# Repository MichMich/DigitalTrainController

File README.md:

# DigitalTrainController

This repository contains all the sourcecode as well as the KiCad project for the [Digital Train Controller](http://michaelteeuw.nl/tagged/trainautomator) i built for my dad's model train. 

For more info about this project, check out my blog: http://michaelteeuw.nl/tagged/trainautomator

Feel free to use this code and PCB project, but keep in mind that it comes without ANY form of support. :)

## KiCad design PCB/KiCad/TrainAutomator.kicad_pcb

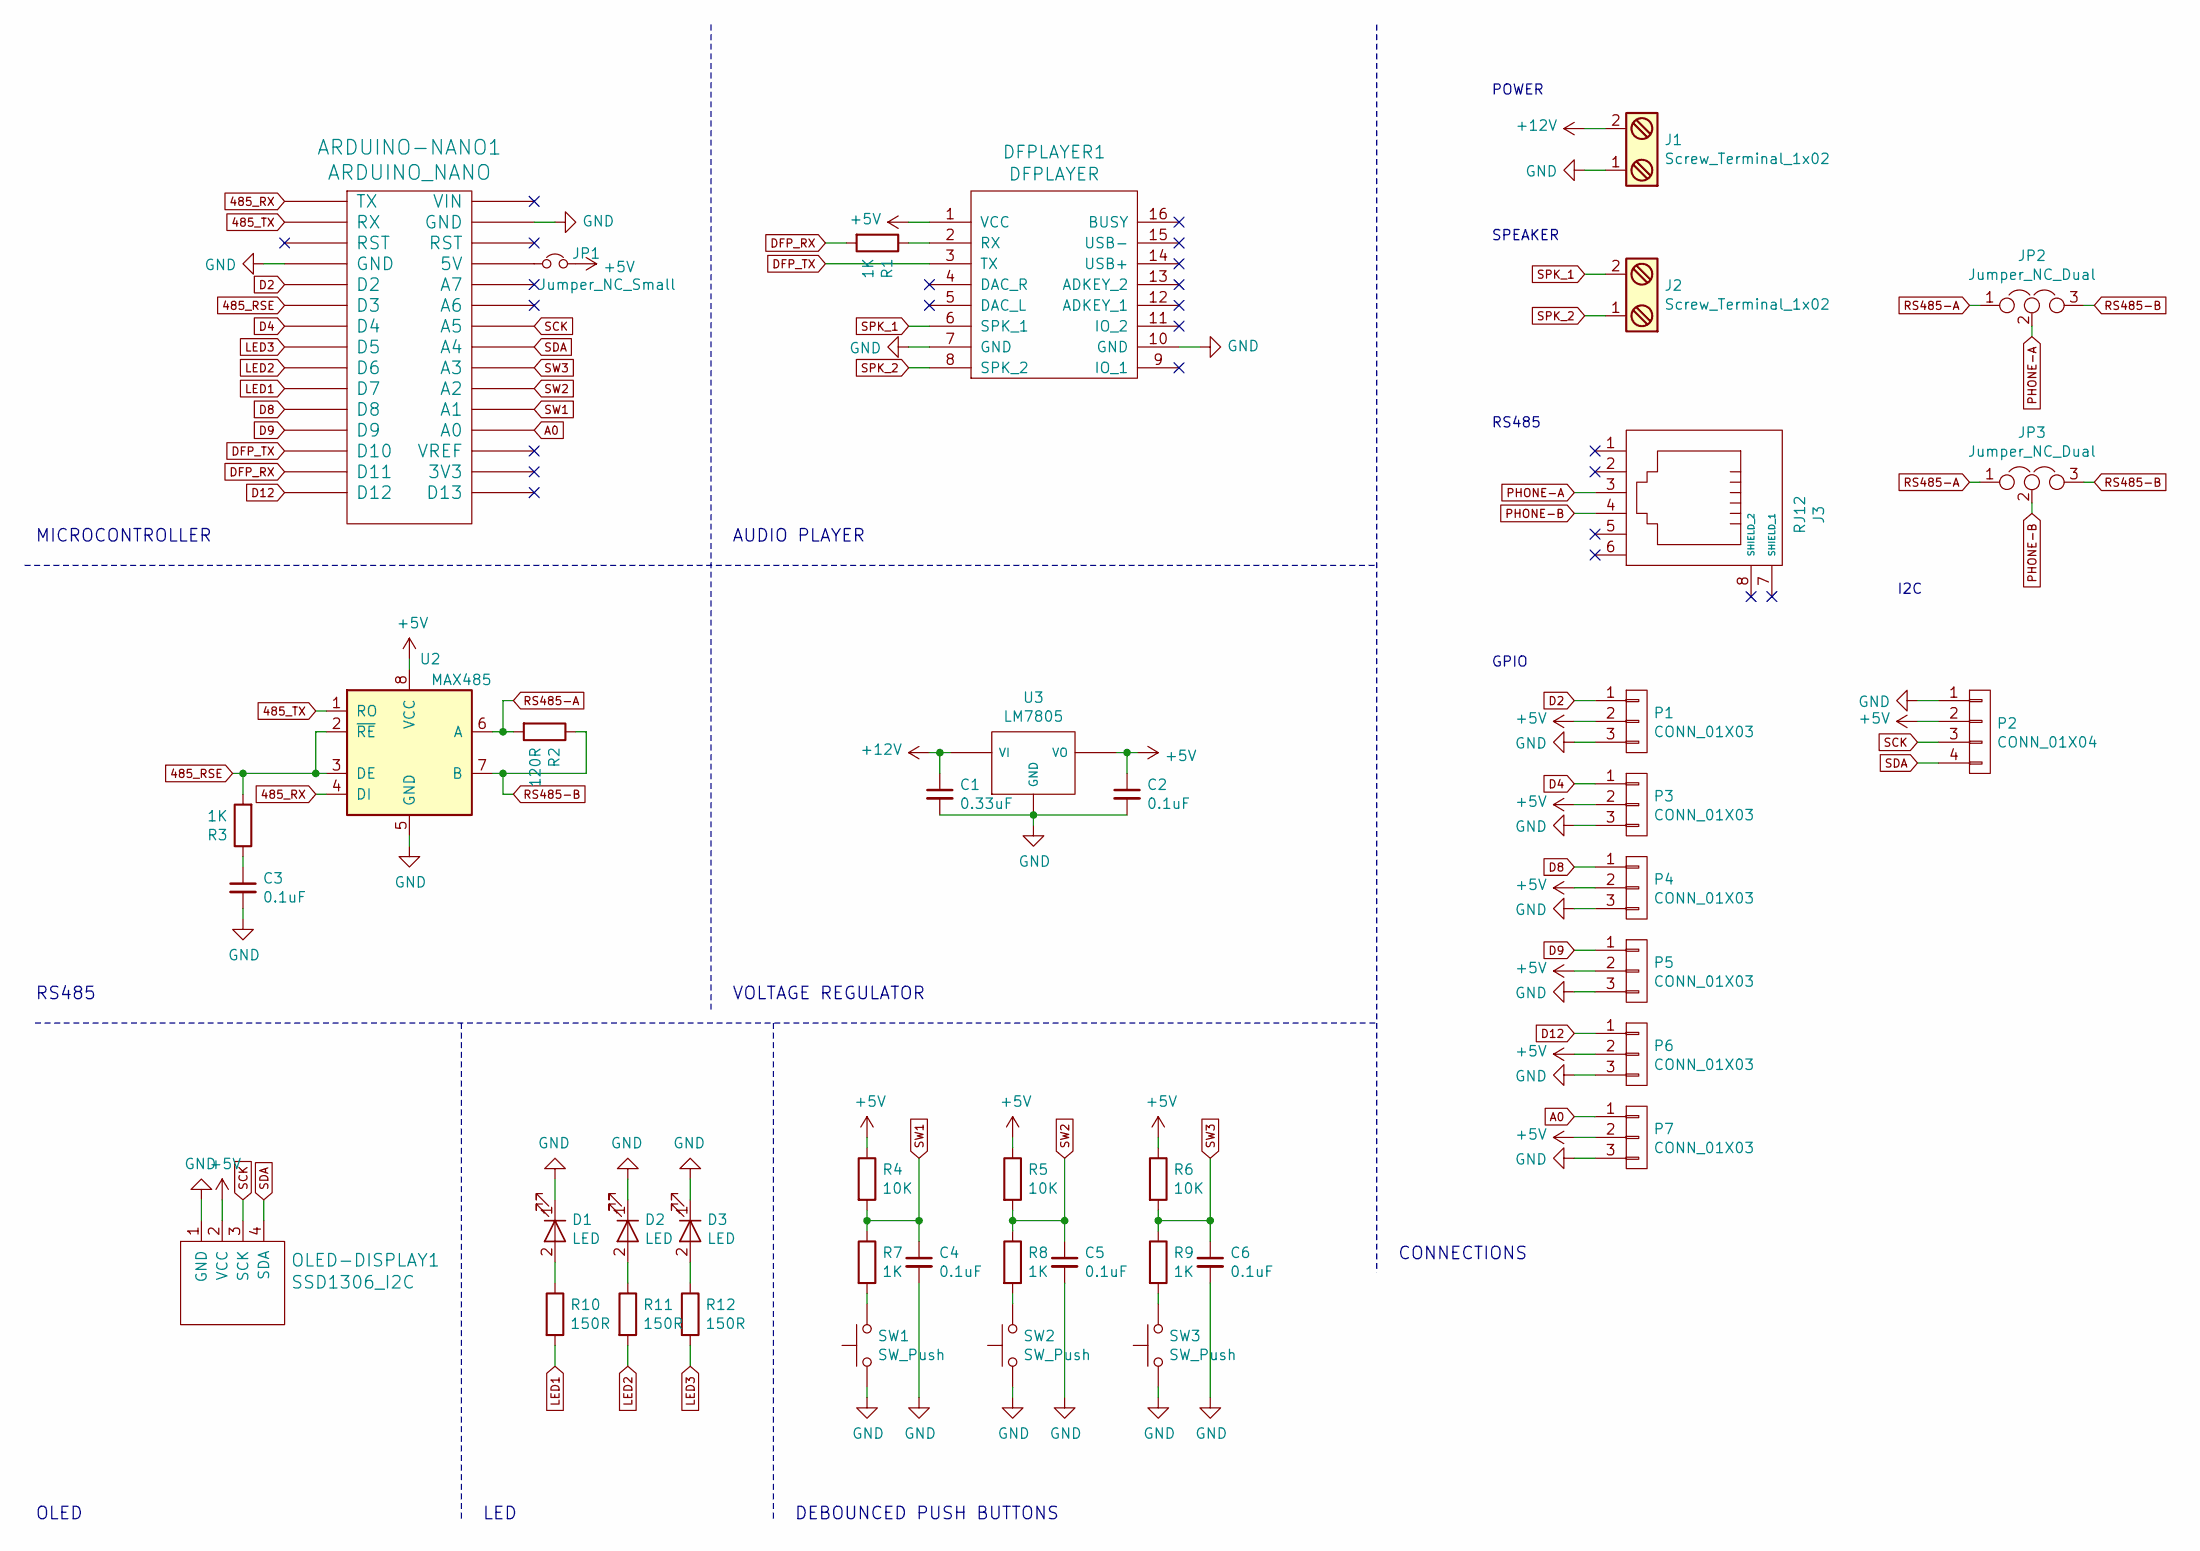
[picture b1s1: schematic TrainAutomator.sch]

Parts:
ARDUINO-NANO1: ARDUINO_NANO; ArduinoNano
C1: 0.33uF; C_0805_HandSoldering
C2, C3, C4, C5, C6: 0.1uF; C_0805_HandSoldering
D1, D2, D3: LED; LED_1206_HandSoldering
DFPLAYER1: DFPLAYER; DFPlayerMini
J1, J2: Screw_Terminal_1x02; TerminalBlock_4UCON_19963_02x3.5mm_Straight
J3: RJ12
JP1: Jumper_NC_Small; Pin_Header_Straight_1x02_Pitch2.00mm
JP2, JP3: Jumper_NC_Dual; DualJumper-NC
OLED-DISPLAY1: SSD1306_I2C; SSD1306-096-OLED-I2C
P1, P3, P4, P5, P6, P7: CONN_01X03; JST_PH_S3B-PH-K_03x2.00mm_Angled
P2: CONN_01X04; JST_PH_S4B-PH-K_04x2.00mm_Angled
R1, R3, R7, R8, R9: 1K; R_0805_HandSoldering
R2: 120R; R_0805_HandSoldering
R4, R5, R6: 10K; R_0805_HandSoldering
R10, R11, R12: 150R; R_0805_HandSoldering
SW1, SW2, SW3: SW_Push; SW_SPST_EVQPE1
U2: MAX485; SOIC-8_3.9x4.9mm_Pitch1.27mm
U3: LM7805; TO-263-2

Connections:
485_RSE: ARDUINO-NANO1.6 (D3), R3.2, U2.2 (~RE~), U2.3 (DE)
485_RX: ARDUINO-NANO1.1 (TX), U2.4 (DI)
485_TX: ARDUINO-NANO1.2 (RX), U2.1 (RO)
+5V: C2.1, DFPLAYER1.1 (VCC), JP1.2, OLED-DISPLAY1.2 (VCC), P1.2, P2.2, P3.2, P4.2, P5.2, P6.2, P7.2, R4.1, R5.1, R6.1, U2.8 (VCC), U3.3 (VO)
+12V: C1.1, J1.2, U3.1 (VI)
A0: ARDUINO-NANO1.19 (A0), P7.1
D2: ARDUINO-NANO1.5 (D2), P1.1
D4: ARDUINO-NANO1.7 (D4), P3.1
D8: ARDUINO-NANO1.11 (D8), P4.1
D9: ARDUINO-NANO1.12 (D9), P5.1
D12: ARDUINO-NANO1.15 (D12), P6.1
DFP_RX: ARDUINO-NANO1.14 (D11), R1.2
DFP_TX: ARDUINO-NANO1.13 (D10), DFPLAYER1.3 (TX)
GND: ARDUINO-NANO1.4 (GND), ARDUINO-NANO1.29 (GND), C1.2, C2.2, C3.2, C4.2, C5.2, C6.2, D1.1 (K), D2.1 (K), D3.1 (K), DFPLAYER1.7 (GND), DFPLAYER1.10 (GND), J1.1, OLED-DISPLAY1.1 (GND), P1.3, P2.1, P3.3, P4.3, P5.3, P6.3, P7.3, SW1.1, SW2.1, SW3.1, U2.5 (GND), U3.2 (GND)
LED1: ARDUINO-NANO1.10 (D7), R10.2
LED2: ARDUINO-NANO1.9 (D6), R11.2
LED3: ARDUINO-NANO1.8 (D5), R12.2
unnamed: ARDUINO-NANO1.27 (5V), JP1.1
unnamed: C3.1, R3.1
unnamed: D1.2 (A), R10.1
unnamed: D2.2 (A), R11.1
unnamed: D3.2 (A), R12.1
unnamed: DFPLAYER1.2 (RX), R1.1
unnamed: R7.2, SW1.2
unnamed: R8.2, SW2.2
unnamed: R9.2, SW3.2
PHONE-A: J3.3, JP2.2
PHONE-B: J3.4, JP3.2
RS485-A: JP2.1, JP3.1, R2.2, U2.6 (A)
RS485-B: JP2.3, JP3.3, R2.1, U2.7 (B)
SCK: ARDUINO-NANO1.24 (A5), OLED-DISPLAY1.3 (SCK), P2.3
SDA: ARDUINO-NANO1.23 (A4), OLED-DISPLAY1.4 (SDA), P2.4
SPK_1: DFPLAYER1.6 (SPK_1), J2.2
SPK_2: DFPLAYER1.8 (SPK_2), J2.1
SW1: ARDUINO-NANO1.20 (A1), C4.1, R4.2, R7.1
SW2: ARDUINO-NANO1.21 (A2), C5.1, R5.2, R8.1
SW3: ARDUINO-NANO1.22 (A3), C6.1, R6.2, R9.1

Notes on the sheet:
MICROCONTROLLER
RS485
OLED
LED
DEBOUNCED PUSH BUTTONS
VOLTAGE REGULATOR
AUDIO PLAYER
CONNECTIONS
GPIO
RS485
SPEAKER
POWER
I2C

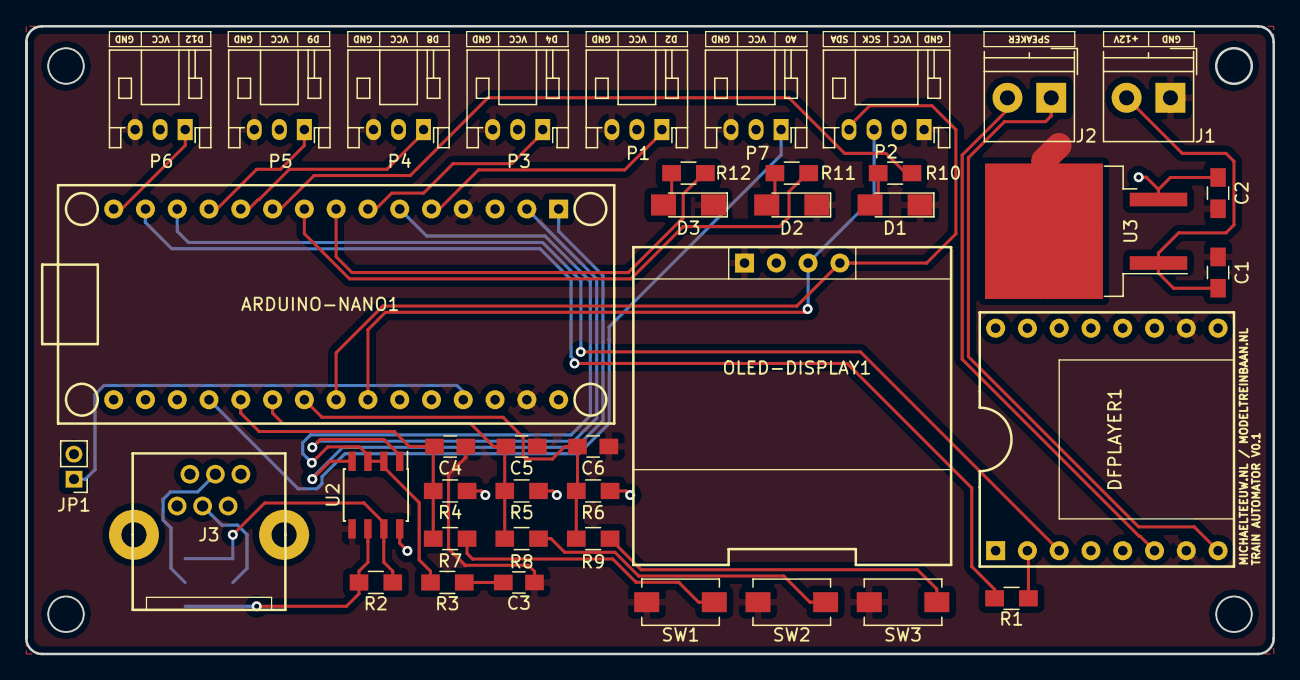
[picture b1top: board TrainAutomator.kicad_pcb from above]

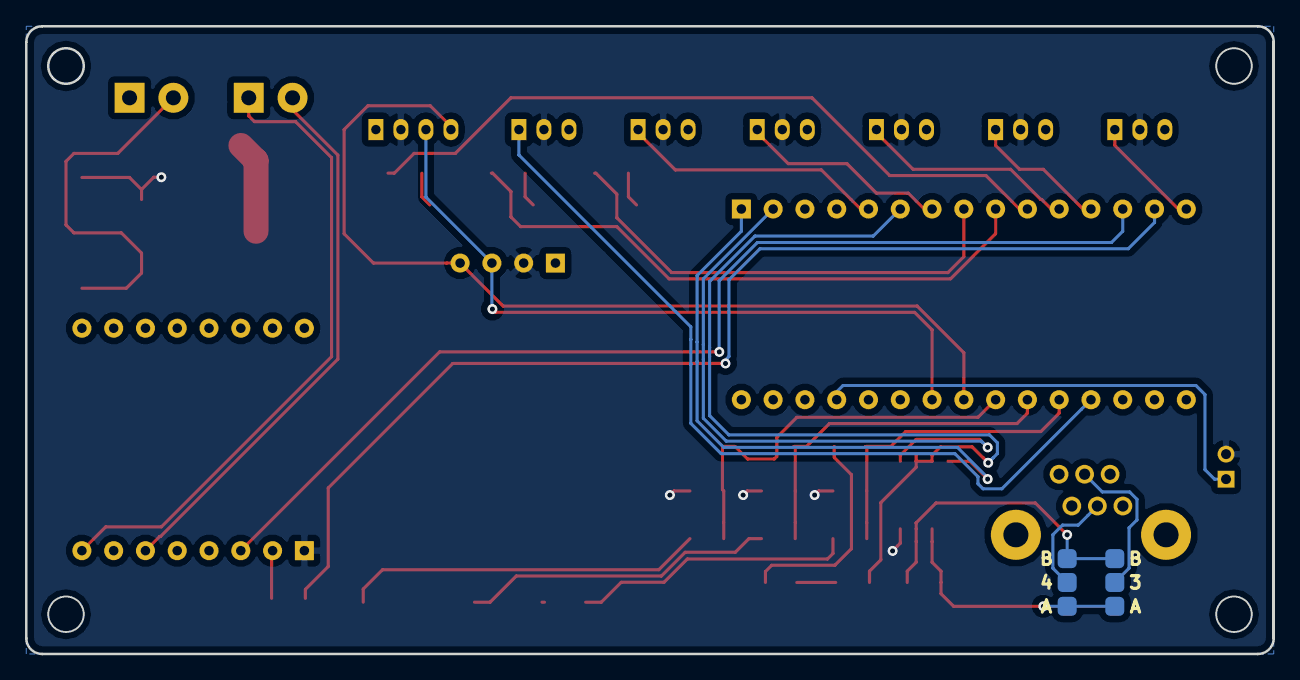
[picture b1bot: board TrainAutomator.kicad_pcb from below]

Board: 2 copper layers, 99.7 x 50.2 mm, 42 parts (2 on the bottom side), 37 nets.

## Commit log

2017-08-13 Make speed configurable
2018-04-15 Add DFPlayer Lib
2018-04-15 Audio play test.
2018-04-15 Sounds
2018-04-23 Start of interface.
2018-04-24 Refactor Display
2018-04-24 Scheduler and audio implementation.
2018-04-25 Seperate sound timers.
2018-04-25 Add TrainController.
2018-04-26 Minor tweaks.
2018-04-27 SettingsManager
2018-04-28 Settings Screen
2018-04-28 Show drive indicator.
2018-04-28 Indicator and fixes minor issues.
2018-05-03 Rotate Screen
2018-07-14 Add PCB files.
